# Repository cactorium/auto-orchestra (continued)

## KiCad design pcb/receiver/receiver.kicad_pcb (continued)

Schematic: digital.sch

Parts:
C301: 1 uF; C_0603_HandSoldering; Mouser 710-885012106022
C302, C303, C304, C305, C306, C307, C308, C309, C312, C316, C317, C318, C320, C321: 100 nF; C_0603_HandSoldering; Mouser 710-885012206071
C310: 4.7 uF; CP_Elec_4x5.3; Mouser 647-UWX1E4R7MCL1
C311: 1 nF; C_0402; Mouser 710-885012205061
C313: 100 pF; C_0402; Mouser 963-UMK105CH101JVHF
C314, C315, C319: 10 uF; C_0805_HandSoldering; Mouser 81-GRM21BR61E106MA3L
C322, C323: 22 pF; C_0402; Mouser 710-885012005009
D301: D_Schottky
D302, D303: 2SS100L-W
D304, D305, D306: TPD1E04U04DPYR
J301, J303: Conn_01x03
J302: Conn_01x04
J304: USB_B_Micro
R301, R302, R305: 0 DNP
R303, R304: 0; R_0603_HandSoldering; Mouser 755-SFR03EZPJ000
R306, R307: 1M; R_0603_HandSoldering; Mouser 603-RC0603JR-071ML
R308: 47k; R_0603_HandSoldering; Mouser 603-RC0603FR-0747KL
R309: 33; R_0603_HandSoldering; Mouser 755-ESR03EZPJ330
R310, R317: 10k; R_0603_HandSoldering; Mouser 603-RC0603FR-0710KL
R311: 100k DNP
R312, R313: 100k; R_0402; Mouser 603-RC0402JR-13100KL
R314, R315, R316: 330
R318: 10k DNP
U301: ATTINY412-SSNR; Atmel-SOIC150-8; Mouser 556-ATTINY412-SSNR
U302: STM32F070F6P6; ST-TSSOP20; Mouser 511-STM32F070F6P6
U303: MAX11666AUB+T; Maxim-U10E+3; Mouser 700-MAX11666AUB+T
U304: L78L33ABUTR; SOT-89-3_Handsoldering; Mouser 511-L78L33ABU-TR
Y301: ABM3B-8.000MHZ-10-1UT; Crystal_SMD_Abracon_ABM3C-4pin_5.0x3.2mm; Mouser 815-ABM3B-8.0-10-1UT

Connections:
+5V_USB: C320.1, D301.1, D304.1 (K), J304.1 (VBUS), U304.3 (VIN); also elsewhere on the board
/ANALOG_EN: U302.14 (PB1/TIM3_CH4/USART3_RTS/TIM14_CH1/TIM1_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); also elsewhere on the board
/Digital/+3V3A: C312.1, C314.1, C315.1, C316.1, C317.1, D302.1 (K), R306.1, R309.2, U303.4 (REF), U303.5 (VDD)
/Digital/ADC_AIN: C311.1; also elsewhere on the board
/Digital/ADC_MISO: U302.12 (PA6/SPI1_MISO/TIM3_CH1/TIM1_BKIN/TIM16_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), U303.9 (DOUT)
/Digital/ADC_MOSI: R311.1, U302.13 (PA7/SPI1_MOSI/TIM3_CH2/TIM14_CH1/TIM1_C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)
/Digital/ADC_NSS: R313.1, U302.10 (PA4/SPI1_NSS/TIM14_CH1/USART2_CK/USB_NO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), U303.6 (nCS)
/Digital/ADC_SCK: U302.11 (PA5/SPI1_SCK/ADC_IN5), U303.10 (SCLK)
/Digital/AIN1: C313.1, D302.2 (A), D303.1 (K), R308.2, U303.1 (AIN1)
/Digital/ATTINY_RXD: R304.2, R305.2, U301.5 (PA2); also elsewhere on the board
/Digital/ATTINY_TXD: R302.2, R303.2, U301.4 (PA1); also elsewhere on the board
/Digital/DEBUG_RX: R315.1, U302.7 (PA1/USART2_RTS/TIM15_CH1N/USART4_RX/EVE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)
/Digital/DEBUG_TX: R314.1, U302.6 (PA0/USART2_CTS/USART4_TX/RTC__TAMP2/WKU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)
/Digital/GAIN_ADC: U301.3 (PA7); also elsewhere on the board
/Digital/GAIN_PDM: U301.2 (PA6); also elsewhere on the board
/Digital/GAIN_SEL: U301.7 (PA3/EXTCLK); also elsewhere on the board
/Digital/STM32_NRST: C303.1, J302.2, U302.4 (NRST)
/Digital/STM32_RXD: R303.1, R305.1, U302.9 (PA3/USART2_RX/TIM15_CH2/ADC_IN3)
/Digital/STM32_SWCLK: J302.3, U302.20 (PA14/USART2_TX/SWCLK)
/Digital/STM32_SWDIO: J302.4, U302.19 (PA13/IR_OUT/SWDIO/USB_NOE)
/Digital/STM32_TXD: R302.1, R304.1, U302.8 (PA2/USART2_TX/TIM15_CH1/ADC_IN2/WKUP4)
/Digital/UPDI: R316.1, U301.6 (PA0/nRESET/UPDI)
/Digital/USB_DM: D306.1 (K), J304.2 (D-), U302.17 (PA9/USART1_TX/TIM1_CH2/TIM15_BKIN/I2C1_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)
/Digital/USB_DP: D305.1 (K), J304.3 (D+), U302.18 (PA10/USART1_RX/TIM1_CH3/TIM17_BKIN/I2C1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)
GND: C301.2, C302.2, C303.2, C304.2, C305.2, C306.2, C307.2, C308.2, C309.2, C310.2, C312.2, C313.2, C314.2, C315.2, C316.2, C317.2, C318.2, C319.2, C320.2, C321.2, C322.2, C323.2, D303.2 (A), D304.2 (A), D305.2 (A), D306.2 (A), J301.1, J302.1, J303.1, J304.5 (GND), J304.6 (Shield), R307.2, R310.1, R311.2, R312.2, R317.1, U301.8 (GND), U302.15 (VSS), U303.3 (AGND), U303.11 (GPAD), U304.2 (GND), Y301.2, Y301.4; also elsewhere on the board
unnamed: C311.2, R306.2, R307.1, R308.1
unnamed: C322.1, U302.2 (PF0/OSC_IN), Y301.1
unnamed: C323.1, U302.3 (PF1/OSC_OUT), Y301.3
unnamed: J301.2, R314.2
unnamed: J301.3, R315.2
unnamed: J303.2, R316.2
unnamed: R310.2, U303.2 (AIN2)
unnamed: R312.1, U303.7 (CHSEL)
unnamed: R317.2, R318.1, U302.1 (BOOT0/WKUP2/RTC_TAMP1/RTC_TS/RTC_OUT)

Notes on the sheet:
11 mA quiescent, ignoring charging gain input capacitors
<10 mA
1.7 mA
+ 6 mA quiescent

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
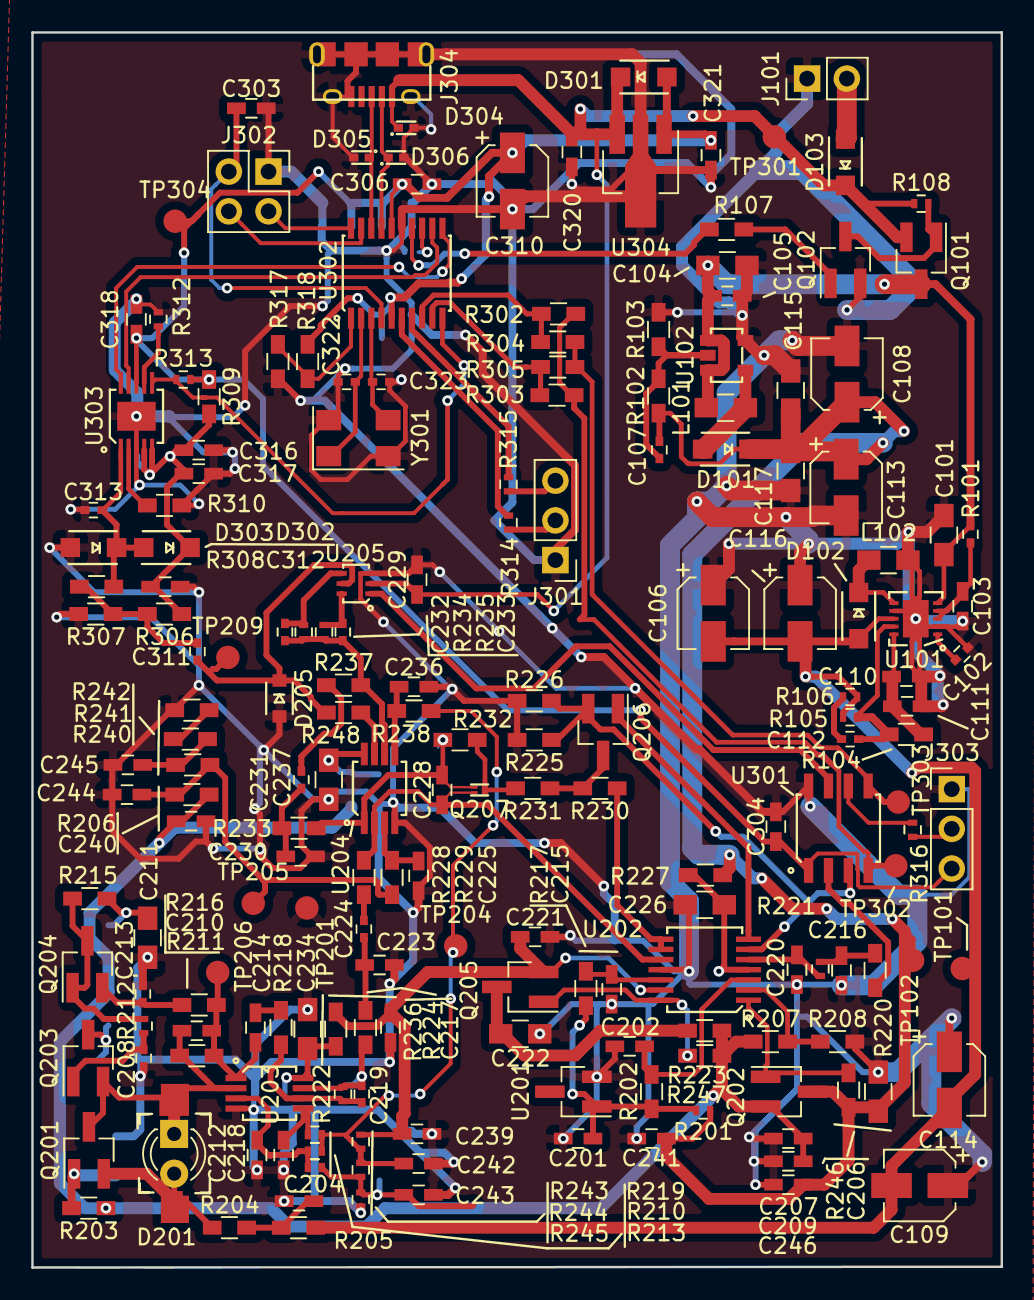
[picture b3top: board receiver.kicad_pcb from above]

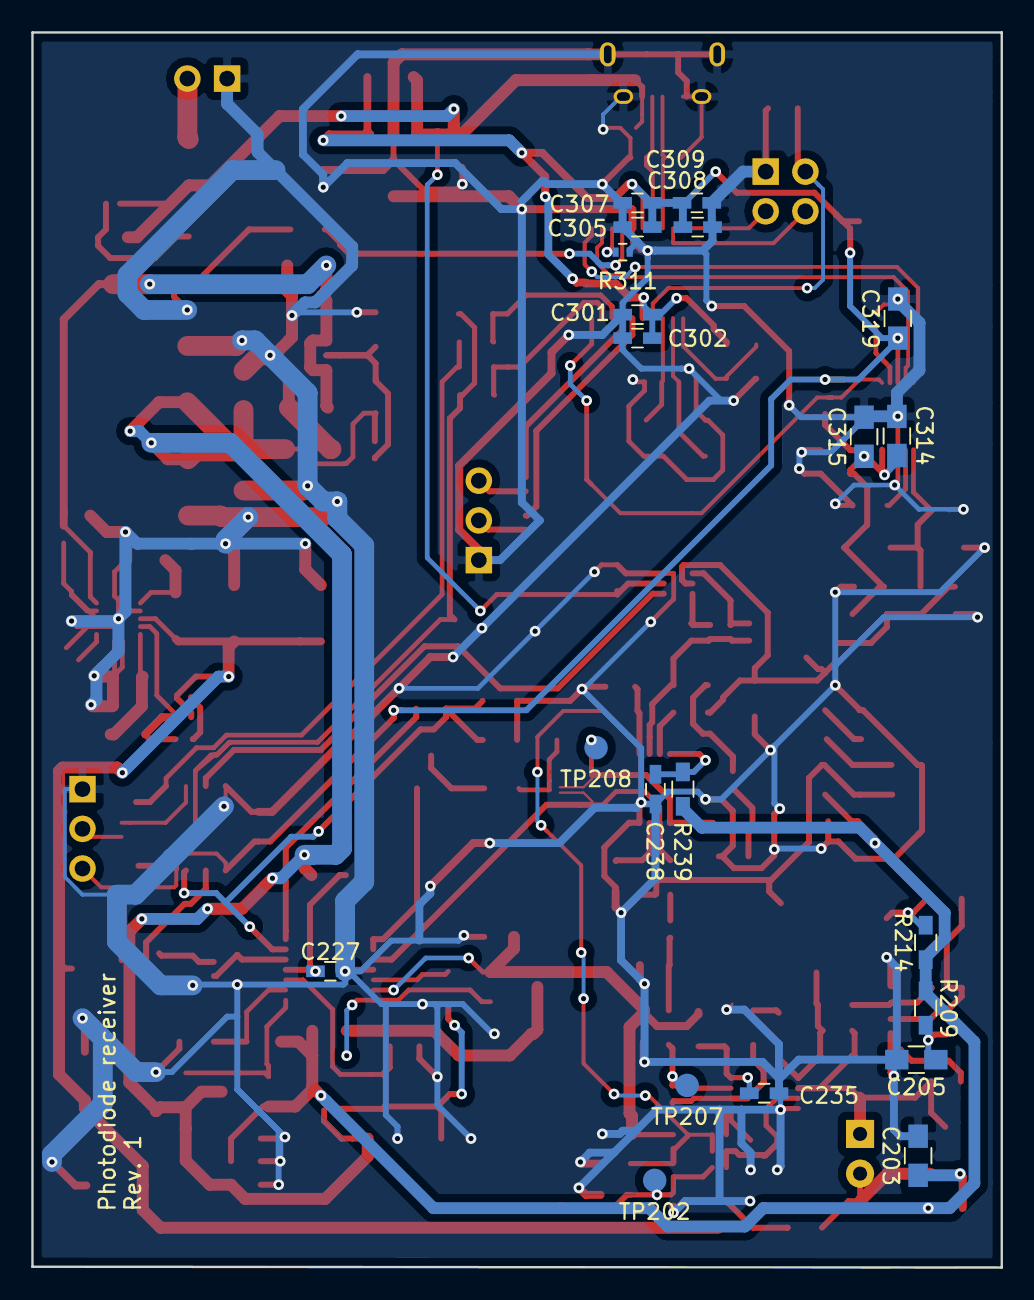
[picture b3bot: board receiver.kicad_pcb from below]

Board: 2 copper layers, 62.0 x 79.0 mm, 214 parts (21 on the bottom side), 99 nets.

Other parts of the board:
TP101, TP102, TP301, TP302, TP303, TP304: TestPoint; Measurement_Point_Round-SMD-Pad_Small

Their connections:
+5V_USB: TP301.1; also elsewhere on the board
+12V: TP102.1; also elsewhere on the board
-12V: TP101.1; also elsewhere on the board
/Digital/ATTINY_RXD: TP303.1; also elsewhere on the board
/Digital/ATTINY_TXD: TP302.1; also elsewhere on the board

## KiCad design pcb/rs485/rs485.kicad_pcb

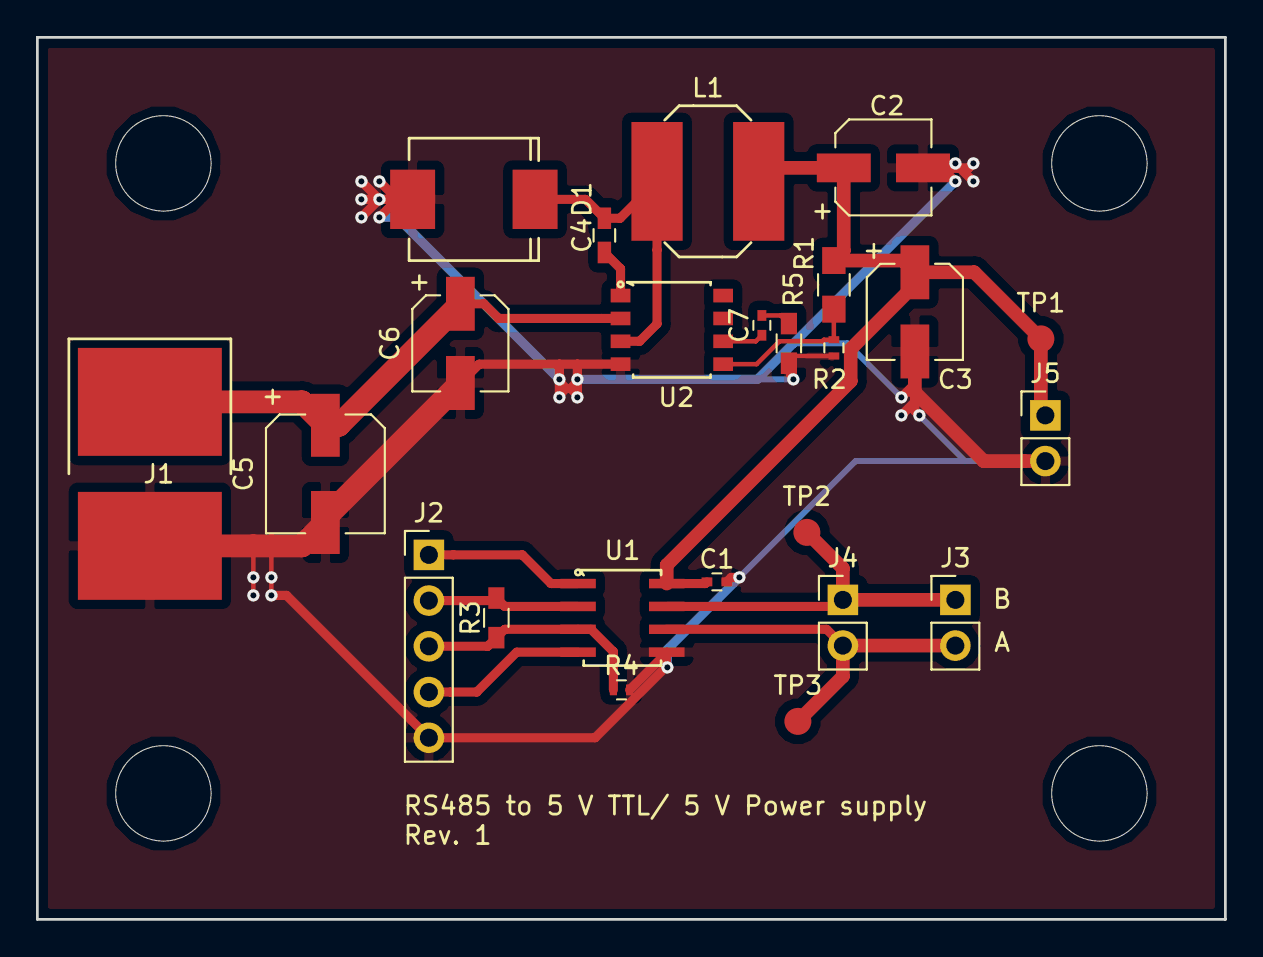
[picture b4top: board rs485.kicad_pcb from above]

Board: 2 copper layers, 66.0 x 49.0 mm, 28 parts (0 on the bottom side), 14 nets.

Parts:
C1: 100nF; C_0402
C2: 100uF; CP_Elec_5x5.3
C3, C6: 10uF; CP_Elec_5x5.7
C4: 10nF; C_0603_HandSoldering
C5: 47uF; CP_Elec_6.3x5.8
C7: 2.2nF; C_0402
D1: VS-MBRS340-M39AT; Wickerlib-DIODE-SMC-DO214AB
J1: Power; Conn-2-8mmx6mm
J2: Conn_01x05; Socket_Strip_Straight_1x05_Pitch2.54mm
J3, J4, J5: Conn_01x02; Socket_Strip_Straight_1x02_Pitch2.54mm
L1: 33uH; Inductor-Bourns-SRN8040TA
MH1, MH2, MH3, MH4: MountingHole; MountingHole_5.3mm_M5
R1: 52k; R_0805_HandSoldering
R2, R4: 10k; R_0402
R3: 0; R_0603_HandSoldering
R5: 12k; R_0603_HandSoldering
TP1, TP2, TP3: TestPoint; Measurement_Point_Round-SMD-Pad_Small
U1: SP485CN-L_TR; Exar-NSOIC8
U2: ACT4065A; ActiveSemi-SOP8

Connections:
/+5V: C1.1, C2.1, C3.1, J5.1, L1.2, R1.1, TP1.1, U1.8
GND: C1.2, C2.2, C3.2, C5.2, C6.2, D1.2, J1.2, J2.5, J5.2, R2.2, R4.2, R5.2, U1.5, U2.4
unnamed: C4.1, U2.1
unnamed: C4.2, D1.1, L1.1, U2.3
unnamed: C5.1, C6.1, J1.1, U2.2
unnamed: C7.1, U2.6
unnamed: C7.2, R5.1
unnamed: J2.1, U1.1
unnamed: J2.2, R3.2, U1.2
unnamed: J2.3, R3.1, R4.1, U1.3
unnamed: J2.4, U1.4
unnamed: J3.1, J4.1, TP2.1, U1.7
unnamed: J3.2, J4.2, TP3.1, U1.6
unnamed: R1.2, R2.1, U2.5

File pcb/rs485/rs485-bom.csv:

Reference,Quantity,Identifier,Package,Value,Tolerance,Voltage,Current,Power,PN,Mouser
"U2","1","","","ACT4065A","","","","","","107-ACT4065ASH-T"
"C4","1","","","10nF","","","","","","77-VJ0603Y103KXAAC"
"C7","1","","","2.2nF","","","","","","710-885012205027"
"R5","1","","","12k","","","","","","603-AC0402JR-078K2L"
"L1","1","","","33uH","","","","","","652-SRN8040TA-330M"
"R1","1","","","52k","","","","","","667-ERJ-6ENF5102V"
"R2;R4","2","","","10k","","","","","","603-RC0402JR-0710KL"
"C2","1","","","100uF","","","","","","710-875105242010"
"D1","1","","","VS-MBRS340-M39AT","","","","","","78-VS-MBRS340-M39AT"
"U1","1","","","SP485CN-L_TR","","","","","","701-SP485CN-L/TR"
"J5;J3;J4","3","","","Conn_01x02","","","","","","NoPart"
"C1","1","","","100nF","","","","","","710-885012105018"
"J1","1","","","Power","","","","","","NoPart"
"TP1;TP2;TP3","3","","","TestPoint","","","","","","NoPart"
"R3","1","","","0","","","","","","755-SFR03EZPJ000"
"MH1;MH2;MH3;MH4","4","","","MountingHole","","","","","","NoPart"
"C5","1","","","47uF","","","","","","647-UWT1V470MCL1S"
"C3;C6","2","","","10uF","","","","","","710-865060542002"
"J2","1","","","Conn_01x05","","","","","","NoPart"

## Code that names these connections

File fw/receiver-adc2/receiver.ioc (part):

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Mcu.Name=STM32F070F6Px
Mcu.Package=TSSOP20
Mcu.UserName=STM32F070F6Px
PA11.Mode=Device
PA11.Signal=USB_DM
PA12.Mode=Device
PA12.Signal=USB_DP
PA13.Mode=Serial_Wire
PA13.Signal=SYS_SWDIO
PA14.Mode=Serial_Wire
PA14.Signal=SYS_SWCLK
PA2.Mode=Asynchronous
PA2.Signal=USART2_TX
PA3.Mode=Asynchronous
PA3.Signal=USART2_RX
PA4.Signal=SPI1_NSS
PA5.Mode=RX_Only_Simplex_Unidirect_Master
PA5.Signal=SPI1_SCK
PA6.Mode=RX_Only_Simplex_Unidirect_Master
PA6.Signal=SPI1_MISO
PB1.Signal=GPIO_Output
PF0-OSC_IN.Mode=HSE-External-Oscillator
PF0-OSC_IN.Signal=RCC_OSC_IN
PF1-OSC_OUT.Mode=HSE-External-Oscillator
PF1-OSC_OUT.Signal=RCC_OSC_OUT
RCC.SYSCLKFreq_VALUE=48000000
RCC.SYSCLKSource=RCC_SYSCLKSOURCE_PLLCLK
board=custom

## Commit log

2018-08-11 Start work on stuff; finish half H bridge
2018-08-11 Save before autofill
2018-08-11 Schematic done; TODO add footprints for connectors
2018-08-12 Save before messing with tiler script
2018-08-13 tile_pcb.py parsing correctly
2018-08-13 Potentially working tile_pcb.py
2018-08-13 Save before tiling
2018-08-13 python tile_pcb.py peripherals.kicad_pcb 3 2,4-9 0.0 30.0
2018-08-13 Save before debugging weird netlist buggery
2018-08-13 Fix bad pad net labeling in tile_pcb.py; python tile_pcb.py peripherals.kicad_pcb 2 3-9 0.0 30.0
2018-08-13 Rename tile_pcb.py to autotile_pcb.py
2018-08-13 Save before testing auto_tile.py
2018-08-13 Autotiling probably works now, aside from breaking from the sheet stuff probably
2018-08-13 Save before autotiling
2018-08-13 python autotile_pcb.py peripherals.kicad_pcb 2 3-9 48.3 63.8 79.9 92.7 0.0 30.0 plus some layout work
2018-08-14 Layout finished and Gerbers generated
2018-08-14 Generate motor driver BOM
2018-08-15 Hopefully all components sourced
2018-08-15 Finish layout
2018-08-15 Add silkscreen name
2018-08-16 Generate BOMs
2018-08-31 Finish schematic, TODO footprinting
2018-08-31 Autofill passives
2018-09-02 Add footprints
2018-09-03 All parts (I think?) sourced and footprinted
2018-09-03 Now all parts footprinted and sourced
2018-09-03 Finish layout and generate Gerbers
2018-09-04 Resize vias
2018-10-12 python2 ~/repos/InteractiveHtmlBom/generate_interactive_bom.py peripherals.kicad_pcb
2018-10-13 Save before autotile
2018-10-13 python autotile_pcb.py peripherals.kicad_pcb 3 2,4-9 47.1 65.8 63.8 77.1 0.0 15.0 also fix autotile_pcb.py to work for Kicad5
2018-10-13 Autotile again, with copying of global traces/vias enabled
2018-10-13 Disable the thing I just did because it wasn't correct
2018-11-09 Redesign peripheral PCB, simulate photodiode circuit
2018-11-23 Add simulation results
2018-11-23 Add README
2018-11-28 Work out signal processing and power sections TODO MCU stuff
2018-11-28 Simulate interstage bandpass filter; performance looks good enough
2018-12-02 Add all components TODO footprint/source everything
2018-12-02 Most parts footprinted; TODO analog voltage reference, photodiodes, passives
2018-12-03 Source most passives; save before autofill
2018-12-03 Autofill components
2018-12-04 Footprint more stuff
2018-12-04 Finish footprinting/sourcing all components
2018-12-04 Most of the layout done TODO add test points for +12V, AVR_UART, various amplifier stage outputs
2018-12-05 Add copper fills and outline, autofill test point footprints, TODO finish placing test points and moving silkscreen
2018-12-05 Finish silkscreen stuff
2018-12-05 (v1) generate Gerbers
2018-12-05 Generate BOM TODO fix gen_mouser.py so that it supports commas in components values correctly
2018-12-05 Regenerate Gerbers
2018-12-05 Small changes/add receiver zip
2018-12-08 (Rev 2) Finish relayout; add load switch and upgrade protection FET, add filter resistors to digital power rails TODO fix up silkscreen
2018-12-09 Finish silkscreen layout
2018-12-09 Generate Gerbers
2018-12-11 Generate interactive BOM
2018-12-11 Updated generated interactive BOM
2018-12-11 Rename peripherals to motor-driver
2018-12-11 Zip transmitter Gerber files for rev 2
2018-12-28 Start work on gain controller firmware
2018-12-28 I guess I modified some of the schematics somewhere?
2018-12-28 Add crt file for now
2018-12-28 Interrupt-based UART messaging seems to be working
2018-12-29 Working ADC stuff
2018-12-29 Receiver PDM first fully functional version TODO test
2018-12-30 Fix missing UART messages, it really doesn't like constant strings so use a different integer encoding
2018-12-30 Note missing components
2019-01-07 Add transmitter firmware to project
2019-01-12 Fix Makefile to work with FT23322H / Arduino Pro Mini programmer
2019-01-13 Stableish control loop; still ~50mV of noise, but this is probably good enough
2019-01-13 Reduce gain a little to improve error maybe; multimeter seems to be messing with measurements
2019-01-17 Add in TODOs for a lot of small mistakes
2019-01-22 First test at receiver firmware; let's see if USB works (TODO test)
2019-01-23 Still not working..
2019-01-23 Switch back to HSE
2019-01-23 Remap pins; still not working
2019-01-23 Add note about ESD diodes
2019-01-23 Try to get gadget0 working
2019-01-24 Save commented out ER_DEBUG version
2019-01-24 Import STMCube-based project
2019-01-24 Shrink USB buffers sizes so it'll actually fit
2019-01-24 Make project flashable; it works! Now to bisect to figure out why it works...
2019-01-24 Working gadget test!
2019-01-24 Working version!
2019-01-24 Fix tabs
2019-01-24 Split USB code into separate file, working timer
2019-01-25 Kind of working data dump
2019-01-25 Plotter seems to work, although it always loses some bytes unless picocom's running
2019-01-25 Add more utils for testing out ADC
2019-01-25 Decimate data and write new plotter
2019-01-26 Fix bug in usart_write, test out accelerometer (failed; guessing the soldering didn't work)
2019-01-26 Add some USB packet processing, first implementation of USART
2019-01-27 Add gain controls
2019-01-27 Increase the sample rate to 100 kHz for now
2019-01-27 Add note for swapping out power supply op amp
2019-01-27 Swap out FSK for BPSK; should be easier to decode
2019-01-27 Accelerometers are working! Add code to process accelerometer data, start work on carrier recovery at ADC
2019-01-27 Fix ADC timing issue; sampling rate was lower than expected
2019-01-27 Rename utils to sw
2019-01-28 Add in some manufacturer stuff for fun
2019-01-28 Collect some samples for carrier recovery testing
2019-01-28 Start work on carrier recovery and rename samples
2019-01-29 Holy shit it's actually working
2019-01-29 Add final stage LPF and make scatter plot selectable as an option
2019-01-29 Add dump IQ option to chain with a line decoder
2019-01-30 Woo, comparator with hysteresis works well for classifying data points. TODO line decoding
2019-01-30 Add decoder; seems to work?
2019-01-31 Work on demodulator; looks like it's missing some bits
2019-01-31 Tweak stuff; working with a really bad BER
2019-01-31 Looks like the issue might be buffer overflow in the TX firmware; the last couple bytes seem to get overwritten pretty often, and the timing seems to support this
2019-01-31 Yep, checksum is passing now
2019-01-31 Add decoder to demod binary, TODO test
2019-01-31 Fix synced type in Decoder
2019-02-04 Start work on music arranger; recording seems to be working
2019-02-05 Implement playback
2019-02-05 Slight tweaks
2019-02-06 Save modifications for IMU setup
2019-02-07 Make instruments monophonic, and implement local storage
2019-02-08 Refactor Recorder into an object plus other stuff
2019-02-08 Refactor out offset code, fix bug with track players where the last note would play forever if the player was started during a note
2019-02-09 Get metronome working
